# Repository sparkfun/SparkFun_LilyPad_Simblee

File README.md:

**NOTE:** *This product has been retired from our catalog. If you are looking for more up-to-date info, please check out some of these resources to see how other users are still hacking and improving on this product.*
* *[SparkFun Forum](https://forum.sparkfun.com/)*
* *[Comments Here on GitHub](https://github.com/sparkfun/SparkFun_LilyPad_Simblee/issues)*
* *[IRC Channel](https://www.sparkfun.com/news/263)*

SparkFun LilyPad Simblee Board  
==================

The [Simblee LilyPad Board](https://www.sparkfun.com/products/13633) is a programmable board that allows you to add mobile app functionality via Bluetooth Low Energy (BLE, or Bluetooth 4.0) to your e-textile projects. Unlike other BLE solutions, the Simblee requires no specialized app development skills to realize the phone-side interface: all the necessary coding is done in the Arduino environment and then uploaded to a browser app on the phone.

[  
*LilyPad Simblee Board*](https://www.sparkfun.com/products/13633)

Design files and firmware files for the [LilyPad Simblee Board](https://www.sparkfun.com/products/13633).

Repository Contents
-------------------

* **/hardware** - Eagle PCB layout files
* **/Production** - Files to support SparkFun production

Documentation
--------------
* **[Simblee Concepts](https://learn.sparkfun.com/tutorials/simblee-concepts)** - Information about Simblee
* **[Hookup Guide](https://learn.sparkfun.com/tutorials/simblee-lilypad-hookup-guide)** - Basic hookup guide

License Information
-------------------

All contents of this repository are released under [Creative Commons Share-alike 4.0](http://creativecommons.org/licenses/by-sa/4.0/).

Authors: Mike Hord @ SparkFun Electonics

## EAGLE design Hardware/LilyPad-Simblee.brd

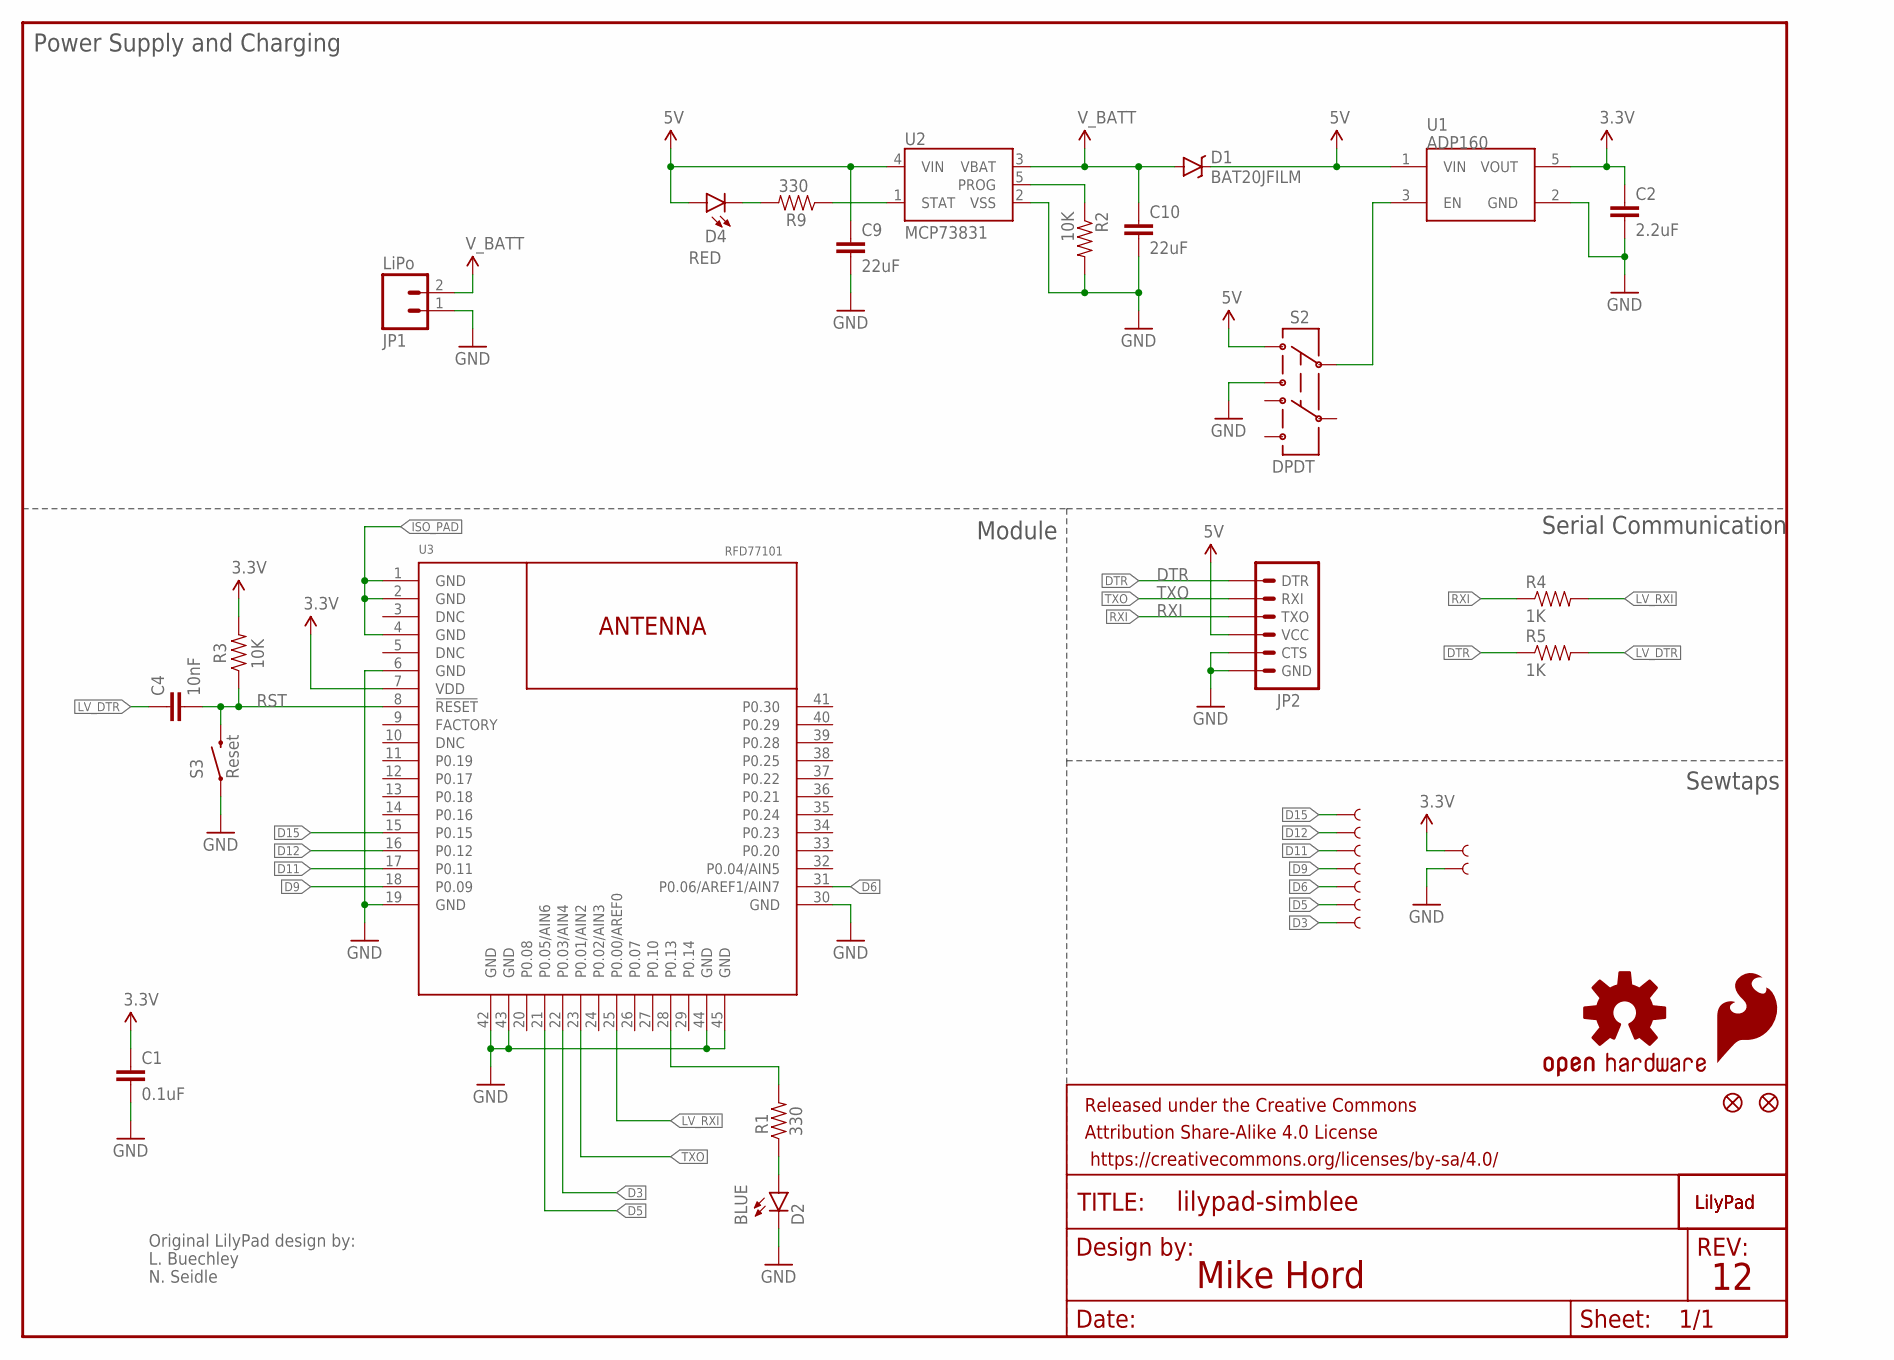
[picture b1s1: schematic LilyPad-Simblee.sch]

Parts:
A4/18, A5/19: SEWTAP9; PETAL-LONG-1-2SIDE
C1: 0.1uF; 0603-CAP
C2: 2.2uF; 0603-CAP
C4: 10nF; 0603-CAP
C9, C10: 22uF; 0805
D1: BAT20JFILM; SOD-323
D2: BLUE; LED-0603
D4: RED; LED-0603
FID1, FID2: FIDUCIALUFIDUCIAL; MICRO-FIDUCIAL
FRAME1: FRAME-LETTER; CREATIVE_COMMONS
JP1: LiPo; JST-2-SMD
JP2: ARDUINO_SERIAL_PROGRAMSMD; 1X06-SMD
LOGO1: SFE_LOGO_FLAME.1COP; SFE_LOGO_FLAME_COPPER_.1
LOGO2: OSHW-LOGOS-COPPER; OSHW-LOGO-S_COPPER
R1, R9: 330; 0603-RES
R2, R3: 10K; 0603-RES
R4, R5: 1K; 0603-RES
S2: DPDT; AYZ0202
S3: Reset; TACTILE-SWITCH-SMD
U1: ADP160; SOT23-5
U2: MCP73831; SOT23-5
U3: RFD77101
U$1: LOGO-LPL; LOGO-L
U$2: LOGO-LPLP; LOGO-LILYPAD
U$4, U$35, U$37, U$39, U$41, U$43, U$45: SEWTAP9; PETAL-LONG-1-2SIDE

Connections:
3.3V: C1.1, C2.1, R3.2, U1.5 (VOUT), U3.7 (VDD), U$43.1
5V: C9.1, D1.C, D4.A, JP2.4 (VCC), S2.1, U1.1 (VIN), U2.4 (VIN)
D3: A5/19.1, U3.22 (P0.03/AIN4)
D5: U3.21 (P0.05/AIN6), U$39.1
D6: A4/18.1, U3.31 (P0.06/AREF1/AIN7)
D9: U3.18 (P0.09), U$4.1
D11: U3.17 (P0.11), U$45.1
D12: U3.16 (P0.12), U$37.1
D15: U3.15 (P0.15), U$35.1
DTR: JP2.1 (DTR), R5.1
GND: C1.2, C2.2, C9.2, C10.2, D2.C, JP1.1 (2), JP2.5 (CTS), JP2.6 (GND), R2.2, S2.3, S3.1, U1.2 (GND), U2.2 (VSS), U3.6 (GND), U3.19 (GND), U3.30 (GND), U3.42 (GND), U3.43 (GND), U3.44 (GND), U3.45 (GND), U$41.1
ISO_PAD: U3.1 (GND), U3.2 (GND), U3.4 (GND)
LV_DTR: C4.1, R5.2
LV_RXI: R4.2, U3.25 (P0.00/AREF0)
unnamed: R1.2, U3.28 (P0.13)
unnamed: D2.A, R1.1
unnamed: S2.2, U1.3 (EN)
unnamed: D4.C, R9.2
PROG: R2.1, U2.5 (PROG)
RST: C4.2, R3.1, S3.3 (2), U3.8 (!RESET!)
RXI: JP2.3 (TXO), R4.1
STAT: R9.1, U2.1 (STAT)
TXO: JP2.2 (RXI), U3.23 (P0.01/AIN2)
V_BATT: C10.1, D1.A, JP1.2 (1), U2.3 (VBAT)

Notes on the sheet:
Original LilyPad design by:
L. Buechley
N. Seidle
Mike Hord
Serial Communication
Sewtaps
Module
Power Supply and Charging

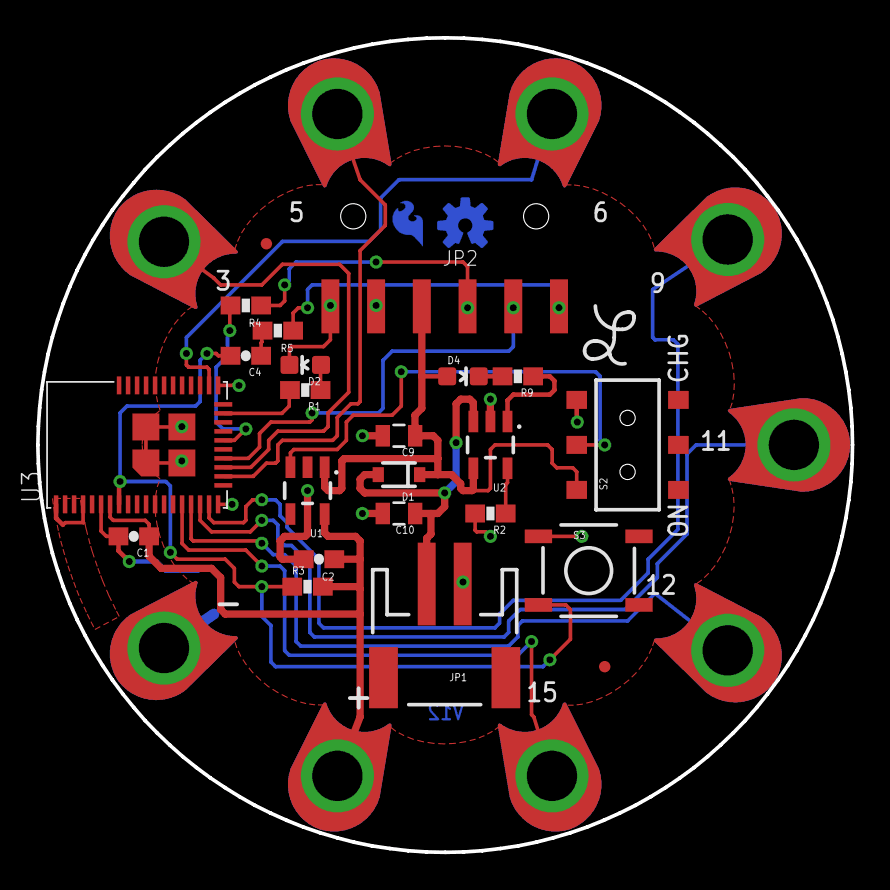
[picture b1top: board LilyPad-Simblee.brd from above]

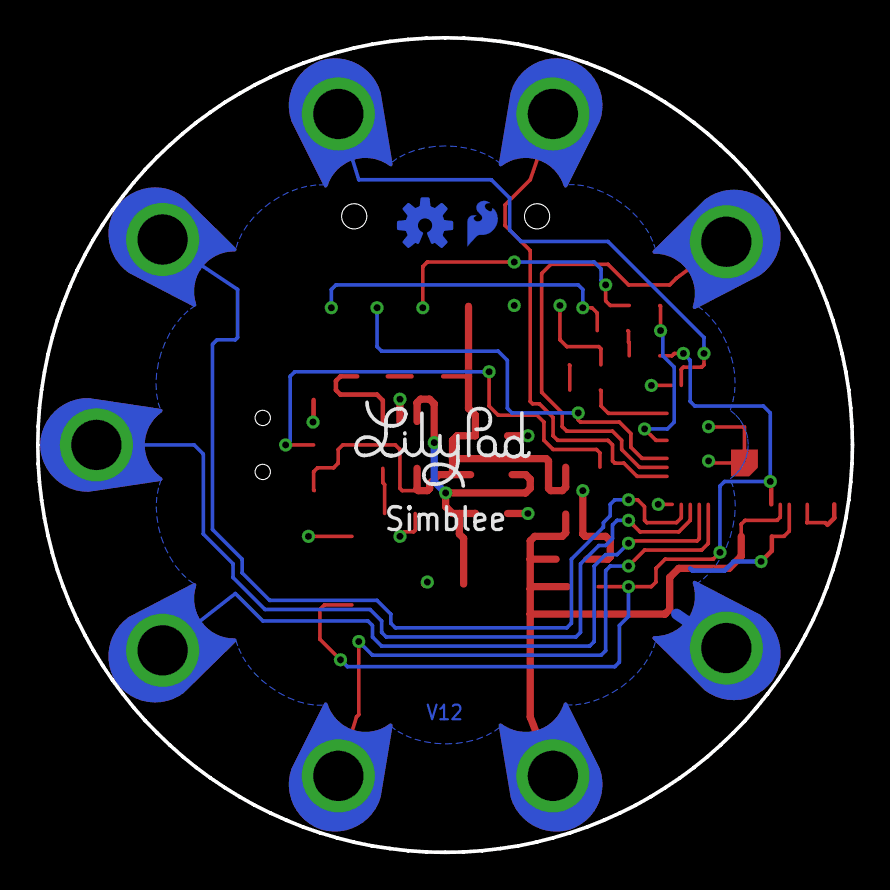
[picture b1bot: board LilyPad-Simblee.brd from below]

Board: 2 copper layers, 45.3 x 45.2 mm, 37 parts (3 on the bottom side), 24 nets.

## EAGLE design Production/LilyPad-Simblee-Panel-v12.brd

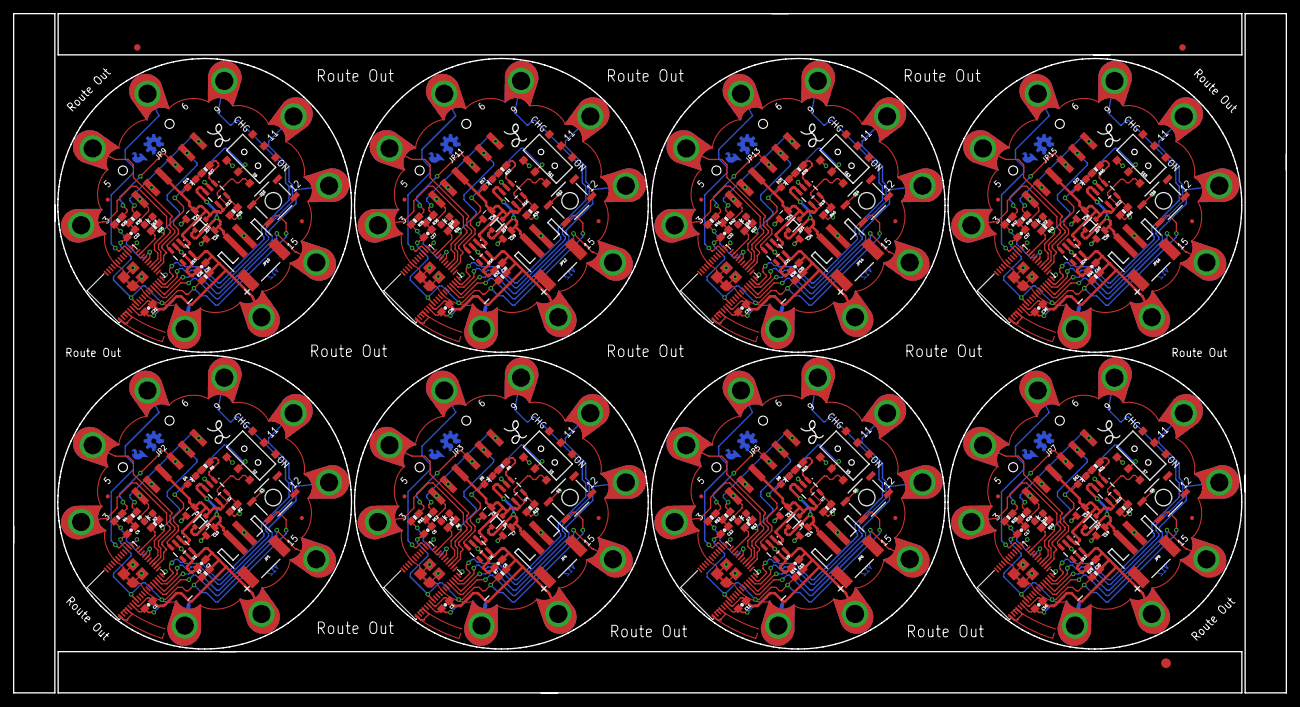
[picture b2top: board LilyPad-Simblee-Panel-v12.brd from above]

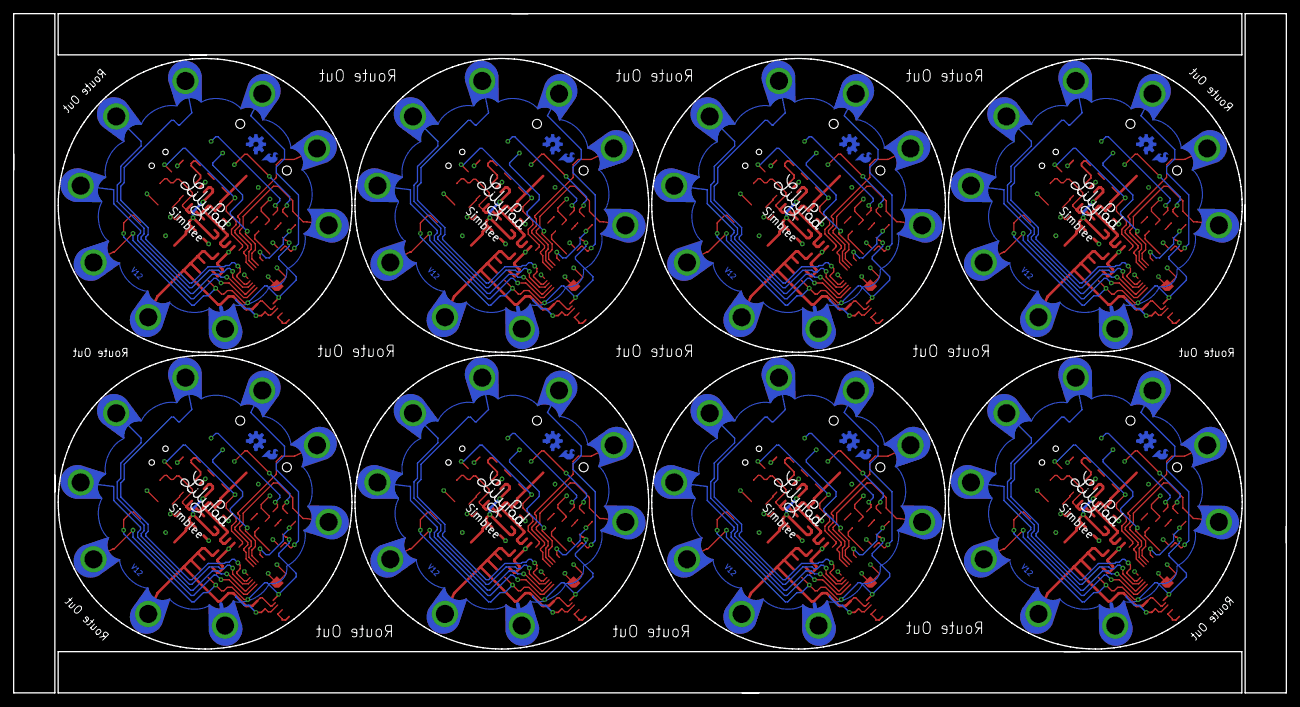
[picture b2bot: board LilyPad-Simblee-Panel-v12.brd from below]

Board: 2 copper layers, 196.1 x 104.6 mm, 291 parts (24 on the bottom side), 192 nets.

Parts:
A4/1, A4/2, A4/3, A4/4, A4/5, A4/6, A4/7, A4/18, A5/1, A5/2, A5/3, A5/4, A5/5, A5/6, A5/7, A5/19: SEWTAP9; PETAL-LONG-1-2SIDE
C1, C3, C11, C16, C21, C26, C31, C36: 0.1uF; 0603-CAP
C2, C8, C15, C20, C25, C30, C35, C40: 2.2uF; 0603-CAP
C4, C5, C12, C17, C22, C27, C32, C37: 10nF; 0603-CAP
C6, C7, C9, C10, C13, C14, C18, C19, C23, C24, C28, C29, C33, C34, C38, C39: 22uF; 0805
D1, D6, D9, D12, D15, D18, D21, D24: BAT20JFILM; SOD-323
D2, D3, D7, D10, D13, D16, D19, D22: BLUE; LED-0603
D4, D5, D8, D11, D14, D17, D20, D23: RED; LED-0603
E$1: FIDUCIAL-1.5X3
E$7, E$8: FIDUCIAL-1X2
FID1, FID2, FID3, FID4, FID5, FID6, FID7, FID8, FID9, FID10, FID11, FID12, FID13, FID14, FID15, FID16: FIDUCIALUFIDUCIAL; MICRO-FIDUCIAL
JP1, JP4, JP6, JP8, JP10, JP12, JP14, JP16: LiPo; JST-2-SMD
JP2, JP3, JP5, JP7, JP9, JP11, JP13, JP15: 1X06-SMD
LOGO1, LOGO3, LOGO5, LOGO7, LOGO9, LOGO11, LOGO13, LOGO15: SFE_LOGO_FLAME.1COP; SFE_LOGO_FLAME_COPPER_.1
LOGO2, LOGO4, LOGO6, LOGO8, LOGO10, LOGO12, LOGO14, LOGO16: OSHW-LOGOS-COPPER; OSHW-LOGO-S_COPPER
R1, R6, R8, R9, R13, R15, R19, R21, R25, R27, R31, R33, R37, R39, R43, R45: 330; 0603-RES
R2, R3, R7, R10, R14, R16, R20, R22, R26, R28, R32, R34, R38, R40, R44, R46: 10K; 0603-RES
R4, R5, R11, R12, R17, R18, R23, R24, R29, R30, R35, R36, R41, R42, R47, R48: 1K; 0603-RES
S1, S2, S5, S7, S9, S11, S13, S15: DPDT; AYZ0202
S3, S4, S6, S8, S10, S12, S14, S16: Reset; TACTILE-SWITCH-SMD
U1, U6, U9, U12, U15, U18, U21, U24: MIC5219 3.3V; SOT23-5
U2, U4, U7, U10, U13, U16, U19, U22: MCP73831; SOT23-5
U3, U5, U8, U11, U14, U17, U20, U23: RFD77101
U$1, U$11, U$20, U$29, U$42, U$53, U$62, U$71: LOGO-LPL; LOGO-L
U$2, U$12, U$21, U$30, U$44, U$54, U$63, U$72: LOGO-LPLP; LOGO-LILYPAD
U$3, U$4, U$5, U$6, U$7, U$8, U$9, U$10, U$13, U$14, U$15, U$16, U$17, U$18, U$19, U$22, U$23, U$24, U$25, U$26, U$27, U$28, U$31, U$32, U$33, U$34, U$35, U$36, U$37, U$38, U$39, U$40, U$41, U$43, U$45, U$46, U$47, U$48, U$49, U$50, U$51, U$52, U$55, U$56, U$57, U$58, U$59, U$60, U$61, U$64, U$65, U$66, U$67, U$68, U$69, U$70: SEWTAP9; PETAL-LONG-1-2SIDE

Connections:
3.3V: C1.1, C2.1, R3.2, U1.5, U3.7, U$43.1
3.3V1: C3.1, C8.1, R7.2, U5.7, U6.5, U$8.1
3.3V2: C11.1, C15.1, R14.2, U8.7, U9.5, U$17.1
3.3V3: C16.1, C20.1, R20.2, U11.7, U12.5, U$26.1
3.3V4: C21.1, C25.1, R26.2, U14.7, U15.5, U$36.1
3.3V5: C26.1, C30.1, R32.2, U17.7, U18.5, U$50.1
3.3V6: C31.1, C35.1, R38.2, U20.7, U21.5, U$59.1
3.3V7: C36.1, C40.1, R44.2, U23.7, U24.5, U$68.1
5V: C9.1, D1.C, D4.A, JP2.4, S2.1, U1.1, U2.4
5V1: C6.1, D5.A, D6.C, JP3.4, S1.1, U4.4, U6.1
5V2: C13.1, D8.A, D9.C, JP5.4, S5.1, U7.4, U9.1
5V3: C18.1, D11.A, D12.C, JP7.4, S7.1, U10.4, U12.1
5V4: C23.1, D14.A, D15.C, JP9.4, S9.1, U13.4, U15.1
5V5: C28.1, D17.A, D18.C, JP11.4, S11.1, U16.4, U18.1
5V6: C33.1, D20.A, D21.C, JP13.4, S13.1, U19.4, U21.1
5V7: C38.1, D23.A, D24.C, JP15.4, S15.1, U22.4, U24.1
D1: A5/1.1, U5.22
D2: U5.21, U$6.1
D3: A5/19.1, U3.22
D4: U5.18, U$10.1
D5: U3.21, U$39.1
D6: A4/18.1, U3.31
D7: U5.17, U$9.1
D8: U5.16, U$5.1
D9: U3.18, U$4.1
D10: U5.15, U$3.1
D11: U3.17, U$45.1
D12: U3.16, U$37.1
D13: A4/1.1, U5.31
D14: A5/2.1, U8.22
D15: U3.15, U$35.1
D16: U8.21, U$15.1
D17: U8.18, U$19.1
D18: U8.17, U$18.1
D19: U8.16, U$14.1
D20: U8.15, U$13.1
D21: A4/2.1, U8.31
D22: A5/3.1, U11.22
D23: U11.21, U$24.1
D24: U11.18, U$28.1
D25: U11.17, U$27.1
D26: U11.16, U$23.1
D27: U11.15, U$22.1
D28: A4/3.1, U11.31
D29: A5/4.1, U14.22
D30: U14.21, U$33.1
D31: U14.18, U$40.1
D32: U14.17, U$38.1
D33: U14.16, U$32.1
D34: U14.15, U$31.1
D35: A4/4.1, U14.31
D36: A5/5.1, U17.22
D37: U17.21, U$48.1
D38: U17.18, U$52.1
D39: U17.17, U$51.1
D40: U17.16, U$47.1
D41: U17.15, U$46.1
D42: A4/5.1, U17.31
D43: A5/6.1, U20.22
D44: U20.21, U$57.1
D45: U20.18, U$61.1
D46: U20.17, U$60.1
D47: U20.16, U$56.1
D48: U20.15, U$55.1
D49: A4/6.1, U20.31
D50: A5/7.1, U23.22
D51: U23.21, U$66.1
D52: U23.18, U$70.1
D53: U23.17, U$69.1
D54: U23.16, U$65.1
D55: U23.15, U$64.1
D56: A4/7.1, U23.31
DTR: JP2.1, R5.1
DTR1: JP3.1, R12.1
DTR2: JP5.1, R18.1
DTR3: JP7.1, R24.1
DTR4: JP9.1, R30.1
DTR5: JP11.1, R36.1
DTR6: JP13.1, R42.1
DTR7: JP15.1, R48.1
GND: C1.2, C2.2, C9.2, C10.2, D2.C, JP1.1, JP2.5, JP2.6, R2.2, S2.3, S3.1, U1.2, U2.2, U3.6, U3.19, U3.30, U3.42, U3.43, U3.44, U3.45, U$41.1
GND1: C3.2, C6.2, C7.2, C8.2, D3.C, JP3.5, JP3.6, JP4.1, R10.2, S1.3, S4.1, U4.2, U5.6, U5.19, U5.30, U5.42, U5.43, U5.44, U5.45, U6.2, U$7.1
GND2: C11.2, C13.2, C14.2, C15.2, D7.C, JP5.5, JP5.6, JP6.1, R16.2, S5.3, S6.1, U7.2, U8.6, U8.19, U8.30, U8.42, U8.43, U8.44, U8.45, U9.2, U$16.1
GND3: C16.2, C18.2, C19.2, C20.2, D10.C, JP7.5, JP7.6, JP8.1, R22.2, S7.3, S8.1, U10.2, U11.6, U11.19, U11.30, U11.42, U11.43, U11.44, U11.45, U12.2, U$25.1
GND4: C21.2, C23.2, C24.2, C25.2, D13.C, JP9.5, JP9.6, JP10.1, R28.2, S9.3, S10.1, U13.2, U14.6, U14.19, U14.30, U14.42, U14.43, U14.44, U14.45, U15.2, U$34.1
GND5: C26.2, C28.2, C29.2, C30.2, D16.C, JP11.5, JP11.6, JP12.1, R34.2, S11.3, S12.1, U16.2, U17.6, U17.19, U17.30, U17.42, U17.43, U17.44, U17.45, U18.2, U$49.1
GND6: C31.2, C33.2, C34.2, C35.2, D19.C, JP13.5, JP13.6, JP14.1, R40.2, S13.3, S14.1, U19.2, U20.6, U20.19, U20.30, U20.42, U20.43, U20.44, U20.45, U21.2, U$58.1
GND7: C36.2, C38.2, C39.2, C40.2, D22.C, JP15.5, JP15.6, JP16.1, R46.2, S15.3, S16.1, U22.2, U23.6, U23.19, U23.30, U23.42, U23.43, U23.44, U23.45, U24.2, U$67.1
ISO_PAD: U3.1, U3.2, U3.4
ISO_PAD1: U5.1, U5.2, U5.4
ISO_PAD2: U8.1, U8.2, U8.4
ISO_PAD3: U11.1, U11.2, U11.4
ISO_PAD4: U14.1, U14.2, U14.4
ISO_PAD5: U17.1, U17.2, U17.4
ISO_PAD6: U20.1, U20.2, U20.4
ISO_PAD7: U23.1, U23.2, U23.4
LV_DTR: C4.1, R5.2
LV_DTR1: C5.1, R12.2
LV_DTR2: C12.1, R18.2
LV_DTR3: C17.1, R24.2
LV_DTR4: C22.1, R30.2
LV_DTR5: C27.1, R36.2
LV_DTR6: C32.1, R42.2
LV_DTR7: C37.1, R48.2
LV_RXI: R4.2, U3.25
LV_RXI1: R11.2, U5.25
LV_RXI2: R17.2, U8.25
LV_RXI3: R23.2, U11.25
LV_RXI4: R29.2, U14.25
LV_RXI5: R35.2, U17.25
LV_RXI6: R41.2, U20.25
LV_RXI7: R47.2, U23.25
unnamed: R1.2, U3.28
unnamed: D2.A, R1.1
unnamed: S2.2, U1.3
unnamed: D3.A, R6.1
unnamed: D5.C, R8.2
unnamed: R6.2, U5.28
unnamed: S1.2, U6.3
unnamed: D4.C, R9.2
unnamed: D7.A, R13.1
unnamed: D8.C, R15.2
unnamed: R13.2, U8.28
unnamed: S5.2, U9.3
unnamed: D10.A, R19.1
unnamed: D11.C, R21.2
unnamed: R19.2, U11.28
unnamed: S7.2, U12.3
unnamed: D13.A, R25.1
unnamed: D14.C, R27.2
unnamed: R25.2, U14.28
unnamed: S9.2, U15.3
unnamed: D16.A, R31.1
unnamed: D17.C, R33.2
unnamed: R31.2, U17.28
unnamed: S11.2, U18.3
unnamed: D19.A, R37.1
unnamed: D20.C, R39.2
unnamed: R37.2, U20.28
unnamed: S13.2, U21.3
unnamed: D22.A, R43.1
unnamed: D23.C, R45.2
unnamed: R43.2, U23.28
unnamed: S15.2, U24.3
PROG: R2.1, U2.5
PROG1: R10.1, U4.5
PROG2: R16.1, U7.5
PROG3: R22.1, U10.5
PROG4: R28.1, U13.5
PROG5: R34.1, U16.5
PROG6: R40.1, U19.5
PROG7: R46.1, U22.5
RST: C4.2, R3.1, S3.3, U3.8
RST1: C5.2, R7.1, S4.3, U5.8
RST2: C12.2, R14.1, S6.3, U8.8
RST3: C17.2, R20.1, S8.3, U11.8
RST4: C22.2, R26.1, S10.3, U14.8
RST5: C27.2, R32.1, S12.3, U17.8
RST6: C32.2, R38.1, S14.3, U20.8
RST7: C37.2, R44.1, S16.3, U23.8
RXI: JP2.3, R4.1
RXI1: JP3.3, R11.1
RXI2: JP5.3, R17.1
RXI3: JP7.3, R23.1
RXI4: JP9.3, R29.1
RXI5: JP11.3, R35.1
RXI6: JP13.3, R41.1
RXI7: JP15.3, R47.1
STAT: R9.1, U2.1
STAT1: R8.1, U4.1
STAT2: R15.1, U7.1
STAT3: R21.1, U10.1
STAT4: R27.1, U13.1
STAT5: R33.1, U16.1
STAT6: R39.1, U19.1
STAT7: R45.1, U22.1
TXO: JP2.2, U3.23
TXO1: JP3.2, U5.23
TXO2: JP5.2, U8.23
TXO3: JP7.2, U11.23
TXO4: JP9.2, U14.23
TXO5: JP11.2, U17.23
TXO6: JP13.2, U20.23
TXO7: JP15.2, U23.23
V_BATT: C10.1, D1.A, JP1.2, U2.3
V_BATT1: C7.1, D6.A, JP4.2, U4.3
V_BATT2: C14.1, D9.A, JP6.2, U7.3
V_BATT3: C19.1, D12.A, JP8.2, U10.3
V_BATT4: C24.1, D15.A, JP10.2, U13.3
V_BATT5: C29.1, D18.A, JP12.2, U16.3
V_BATT6: C34.1, D21.A, JP14.2, U19.3
V_BATT7: C39.1, D24.A, JP16.2, U22.3

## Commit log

2015-06-30 Deleted some superfluous files
2015-07-02 Fixed QC feedback issues.
2015-07-02 Fix tented via
2015-10-13 Necessary changes for reds. Submitting for QC review
2015-10-16 Fixed board thickness note
2015-10-20 Rep D8 w D6, add pour to antenna area, pour to top
2015-10-21 Fix some QC review issues
2015-11-30 Chg to V12, reduce paste on GND pads to 12.5%
2015-12-04 minor movement of fid for better ground pour
2015-12-04 created panel v12
2016-02-04 Release

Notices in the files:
parts and their libraries:
RFDigital: © 2015 RF Digital Corporation
SparkFun-Aesthetics: Licensing: Creative Commons ShareAlike 4.0 International - https://creativecommons.org/licenses/by-sa/4.0
SparkFun-Aesthetics: Released under the Creative Commons Attribution Share-Alike 4.0 License
